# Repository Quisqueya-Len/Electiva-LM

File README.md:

# Electiva-LM
Repositorio correspondiente a la materia Electiva Mecatrónica C3-2024
Autor: Luis Emilio Molina
Enlace al video del proyecto final: https://youtu.be/zNI0fAynepY

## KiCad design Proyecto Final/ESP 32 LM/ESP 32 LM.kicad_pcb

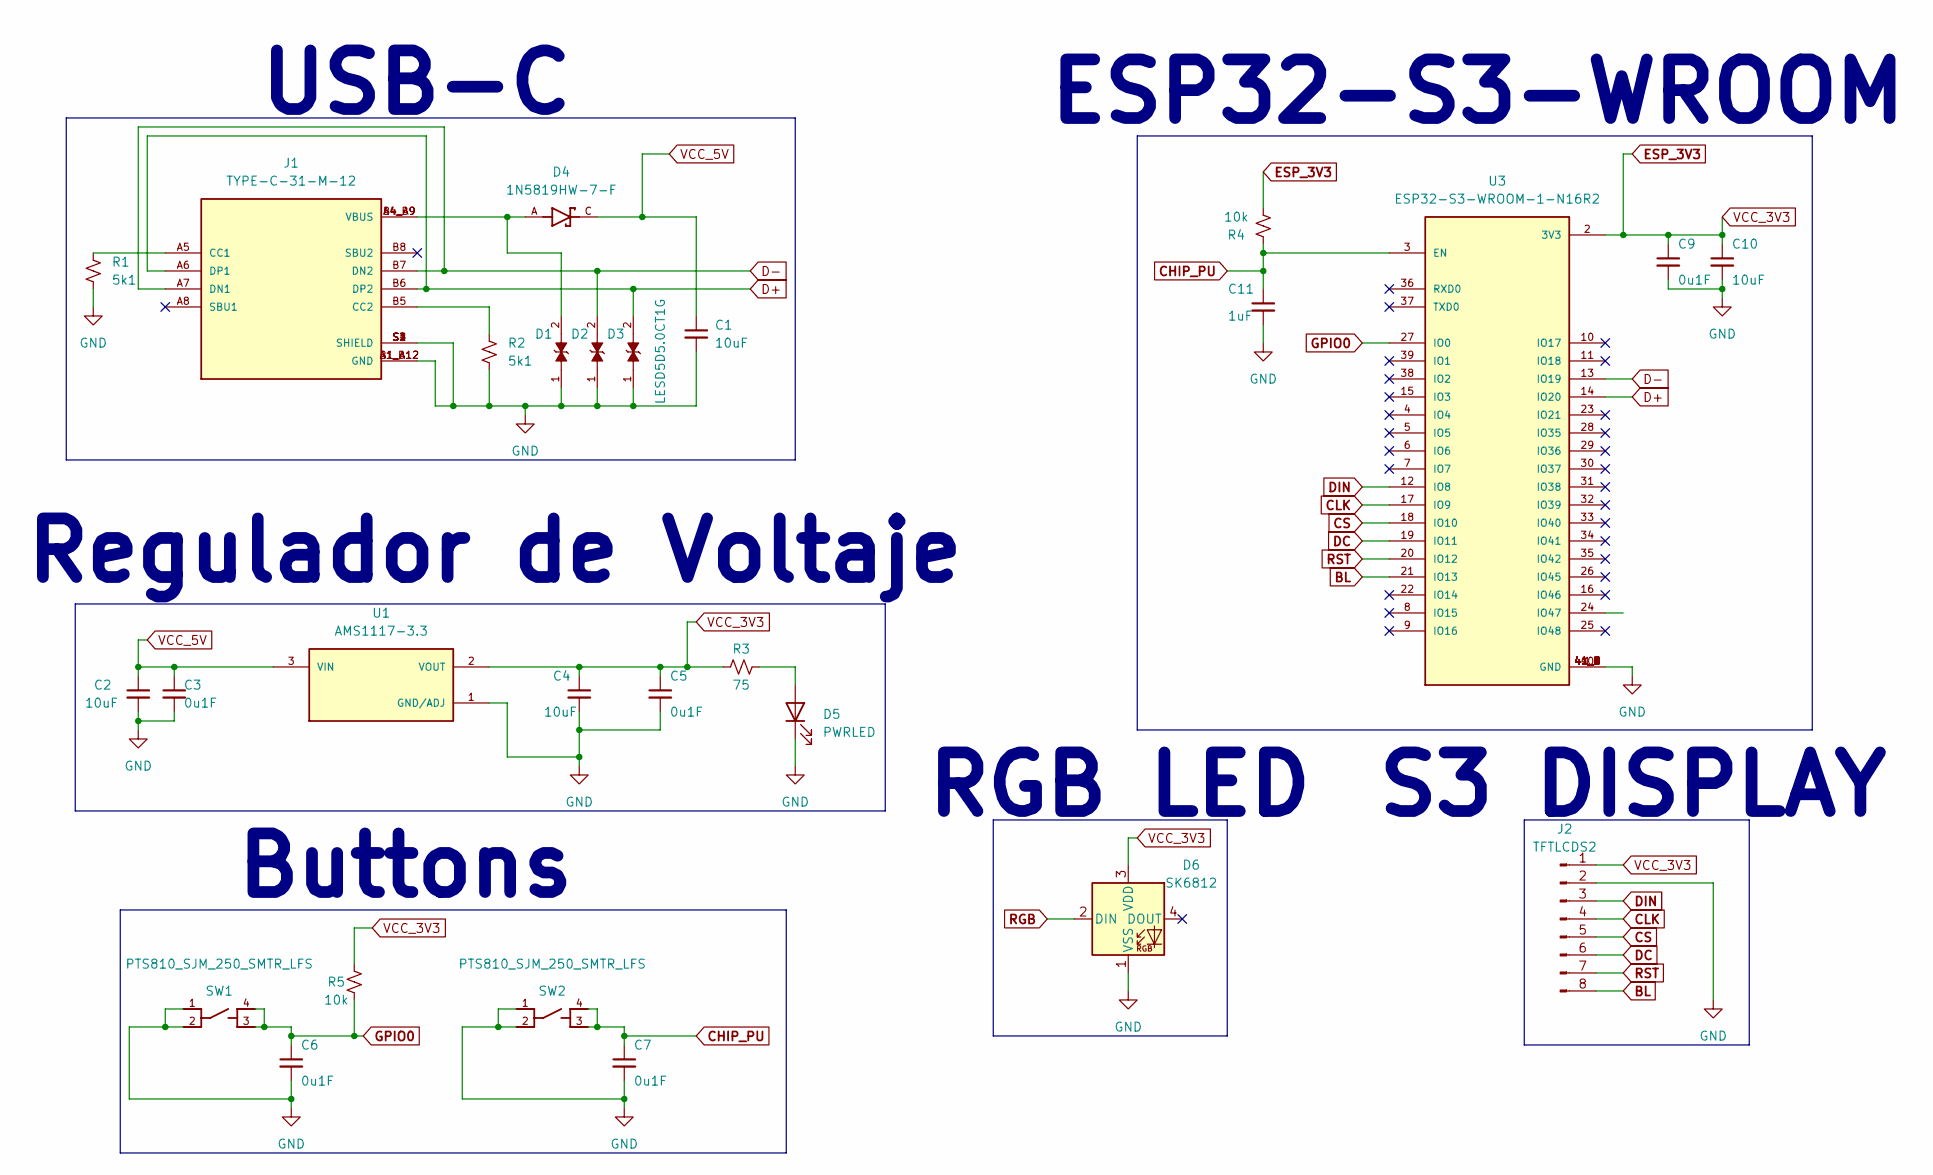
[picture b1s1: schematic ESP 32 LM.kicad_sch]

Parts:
C1, C2, C4, C10: 10uF; C_1206_3216Metric
C3, C5, C6, C7, C9: 0u1F; C_0603_1608Metric
C11: 1uF; C_0603_1608Metric
D1, D2, D3: LESD5D5.0CT1G; TVS_LESD5D5.0CT1G; PARTREV O
D4: 1N5819HW-7-F; SOD3715X145N; PARTREV 18-2
D5: PWRLED; LED_0603_1608Metric
D6: SK6812; LED_SK6812_PLCC4_5.0x5.0mm_P3.2mm
J1: TYPE-C-31-M-12; HRO_TYPE-C-31-M-12; PARTREV 2020.12.08
J2: TFTLCDS2; PinSocket_1x08_P2.54mm_Vertical
R1, R2: 5k1; R_0603_1608Metric
R3: 75; R_0603_1608Metric
R4, R5: 10k; R_0805_2012Metric
SW1, SW2: PTS810_SJM_250_SMTR_LFS; SW_PTS810_SJM_250_SMTR_LFS
U1: AMS1117-3.3; SOT229P700X180-4N; PARTREV N/A
U3: ESP32-S3-WROOM-1-N16R2; XCVR_ESP32-S3-WROOM-1-N16R2; PARTREV v1.0

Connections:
BL: J2.8, U3.21 (IO13)
CHIP_PU: C7.1, C11.1, R4.1, SW2.3, SW2.4, U3.3 (EN)
CLK: J2.4, U3.17 (IO9)
CS: J2.5, U3.18 (IO10)
D+: D3.2, J1.A6 (DP1), J1.B6 (DP2), U3.14 (IO20)
D-: D2.2, J1.A7 (DN1), J1.B7 (DN2), U3.13 (IO19)
DC: J2.6, U3.19 (IO11)
DIN: J2.3, U3.12 (IO8)
ESP_3V3: C4.1, C5.1, C9.1, C10.1, D6.3 (VDD), J2.1, R3.1, R4.2, R5.2, U1.2 (VOUT), U3.2 (3V3)
GND: C1.2, C2.2, C3.2, C4.2, C5.2, C6.2, C7.2, C9.2, C10.2, C11.2, D1.1, D2.1, D3.1, D5.1 (K), D6.1 (VSS), J1.A1_B12 (GND), J1.B1_A12 (GND), J1.S1 (SHIELD), J1.S2 (SHIELD), J1.S3 (SHIELD), J1.S4 (SHIELD), J2.2, R1.2, R2.2, SW1.1, SW1.2, SW2.1, SW2.2, U1.1 (GND/ADJ), U3.1 (GND), U3.40 (GND), U3.41_1 (GND), U3.41_2 (GND), U3.41_3 (GND), U3.41_4 (GND), U3.41_5 (GND), U3.41_6 (GND), U3.41_7 (GND), U3.41_8 (GND), U3.41_9 (GND)
GPIO0: C6.1, R5.1, SW1.3, SW1.4, U3.27 (IO0)
unnamed: D1.2, D4.A, J1.A4_B9 (VBUS), J1.B4_A9 (VBUS)
unnamed: D5.2 (A), R3.2
unnamed: J1.A5 (CC1), R1.1
unnamed: J1.B5 (CC2), R2.1
RGB: D6.2 (DIN)
RST: J2.7, U3.20 (IO12)
VCC_5V: C1.1, C2.1, C3.1, D4.C, U1.3 (VIN)

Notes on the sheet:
USB-C
S3 DISPLAY
Regulador de Voltaje
ESP32-S3-WROOM
RGB LED
Buttons

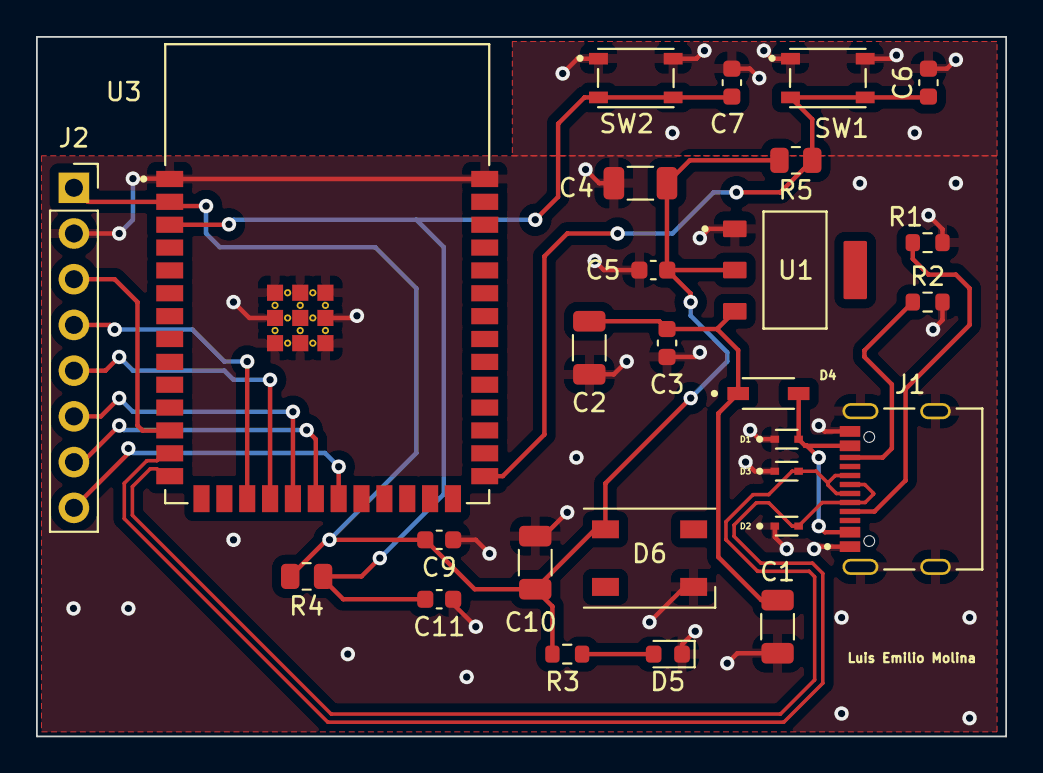
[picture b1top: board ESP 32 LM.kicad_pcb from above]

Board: 2 copper layers, 53.8 x 38.9 mm, 27 parts (0 on the bottom side), 17 nets.

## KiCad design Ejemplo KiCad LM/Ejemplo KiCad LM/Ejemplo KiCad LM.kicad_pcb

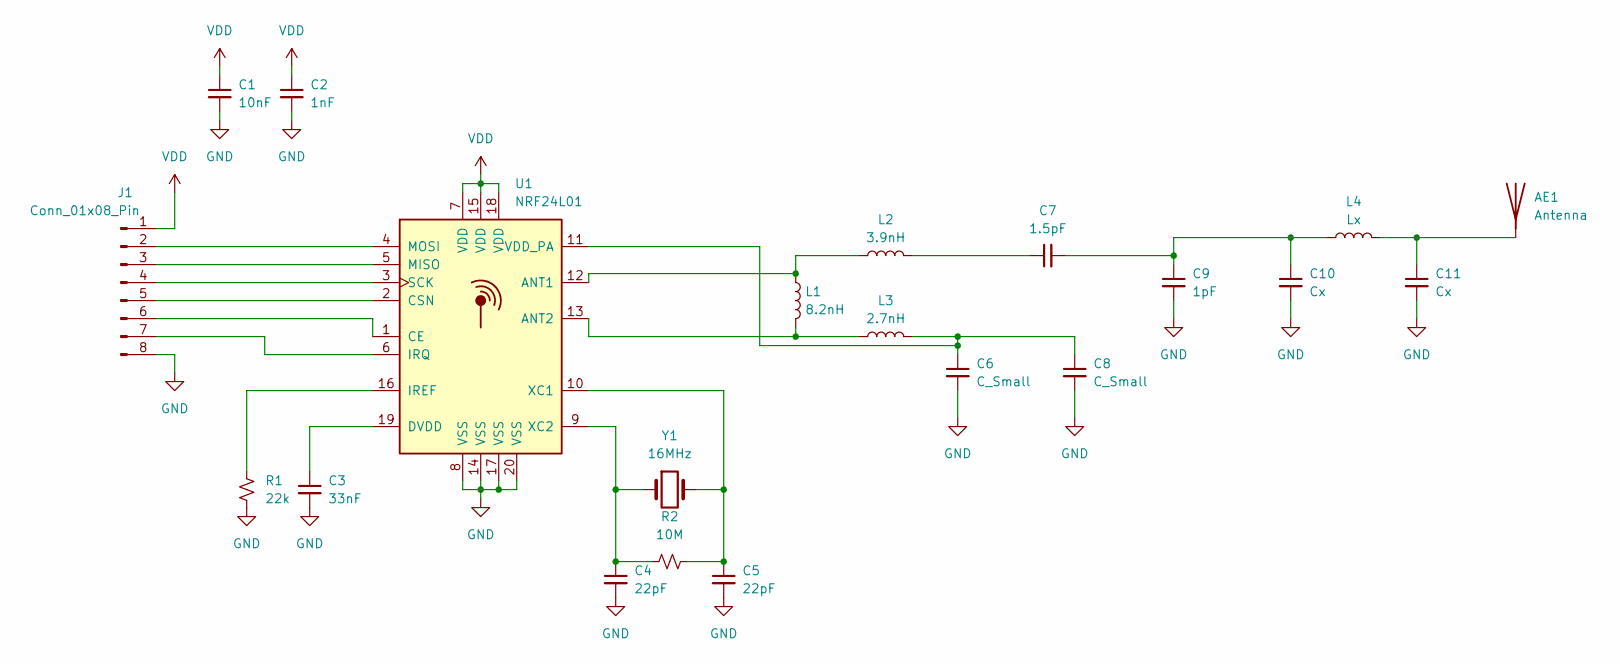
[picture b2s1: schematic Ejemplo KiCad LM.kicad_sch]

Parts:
AE1: Antenna; Texas_SWRA117D_2.4GHz_Right
C1: 10nF; C_0402_1005Metric
C2: 1nF; C_0402_1005Metric
C3: 33nF; C_0402_1005Metric
C4, C5: 22pF; C_0402_1005Metric
C6, C8: C_Small; C_0402_1005Metric
C7: 1.5pF; C_0402_1005Metric
C9: 1pF; C_0402_1005Metric
C10, C11: Cx; C_0402_1005Metric
J1: Conn_01x08_Pin; Hirose_DF13-08P-1.25DSA_1x08_P1.25mm_Vertical
L1: 8.2nH; L_0402_1005Metric
L2: 3.9nH; L_0402_1005Metric
L3: 2.7nH; L_0402_1005Metric
L4: Lx; L_0402_1005Metric
R1: 22k; R_0402_1005Metric
R2: 10M; R_0402_1005Metric
U1: NRF24L01; QFN-20-1EP_4x4mm_P0.5mm_EP2.5x2.5mm
Y1: 16MHz; Crystal_SMD_3215-2Pin_3.2x1.5mm

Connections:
GND: C1.2, C2.2, C3.2, C4.2, C5.2, C6.2, C8.2, C9.2, C10.2, C11.2, J1.8, R1.2, U1.8 (VSS), U1.14 (VSS), U1.17 (VSS), U1.20 (VSS)
unnamed: AE1.1 (A), C11.1, L4.2
unnamed: C7.1, L2.2
unnamed: C7.2, C9.1, C10.1, L4.1
unnamed: J1.2, U1.4 (MOSI)
unnamed: J1.3, U1.5 (MISO)
unnamed: J1.4, U1.3 (SCK)
unnamed: J1.5, U1.2 (CSN)
unnamed: J1.6, U1.1 (CE)
unnamed: J1.7, U1.6 (IRQ)
unnamed: L1.1, L2.1, U1.12 (ANT1)
unnamed: L1.2, L3.1, U1.13 (ANT2)
unnamed: C3.1, U1.19 (DVDD)
unnamed: R1.1, U1.16 (IREF)
unnamed: C6.1, C8.1, L3.2, U1.11 (VDD_PA)
unnamed: C5.1, R2.2, U1.10 (XC1), Y1.2
unnamed: C4.1, R2.1, U1.9 (XC2), Y1.1
VDD: C1.1, C2.1, J1.1, U1.7 (VDD), U1.15 (VDD), U1.18 (VDD)

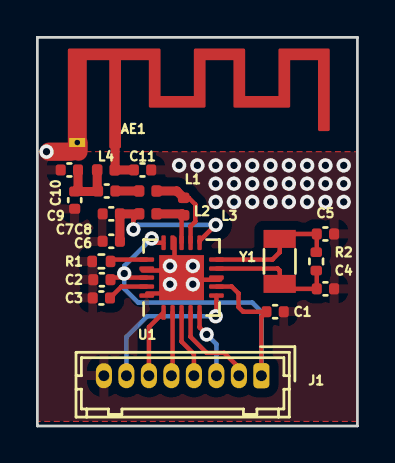
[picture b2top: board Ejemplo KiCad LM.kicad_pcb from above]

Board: 2 copper layers, 17.8 x 21.6 mm, 21 parts (0 on the bottom side), 18 nets.

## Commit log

2024-12-10 Create Ejemplo KiCad
